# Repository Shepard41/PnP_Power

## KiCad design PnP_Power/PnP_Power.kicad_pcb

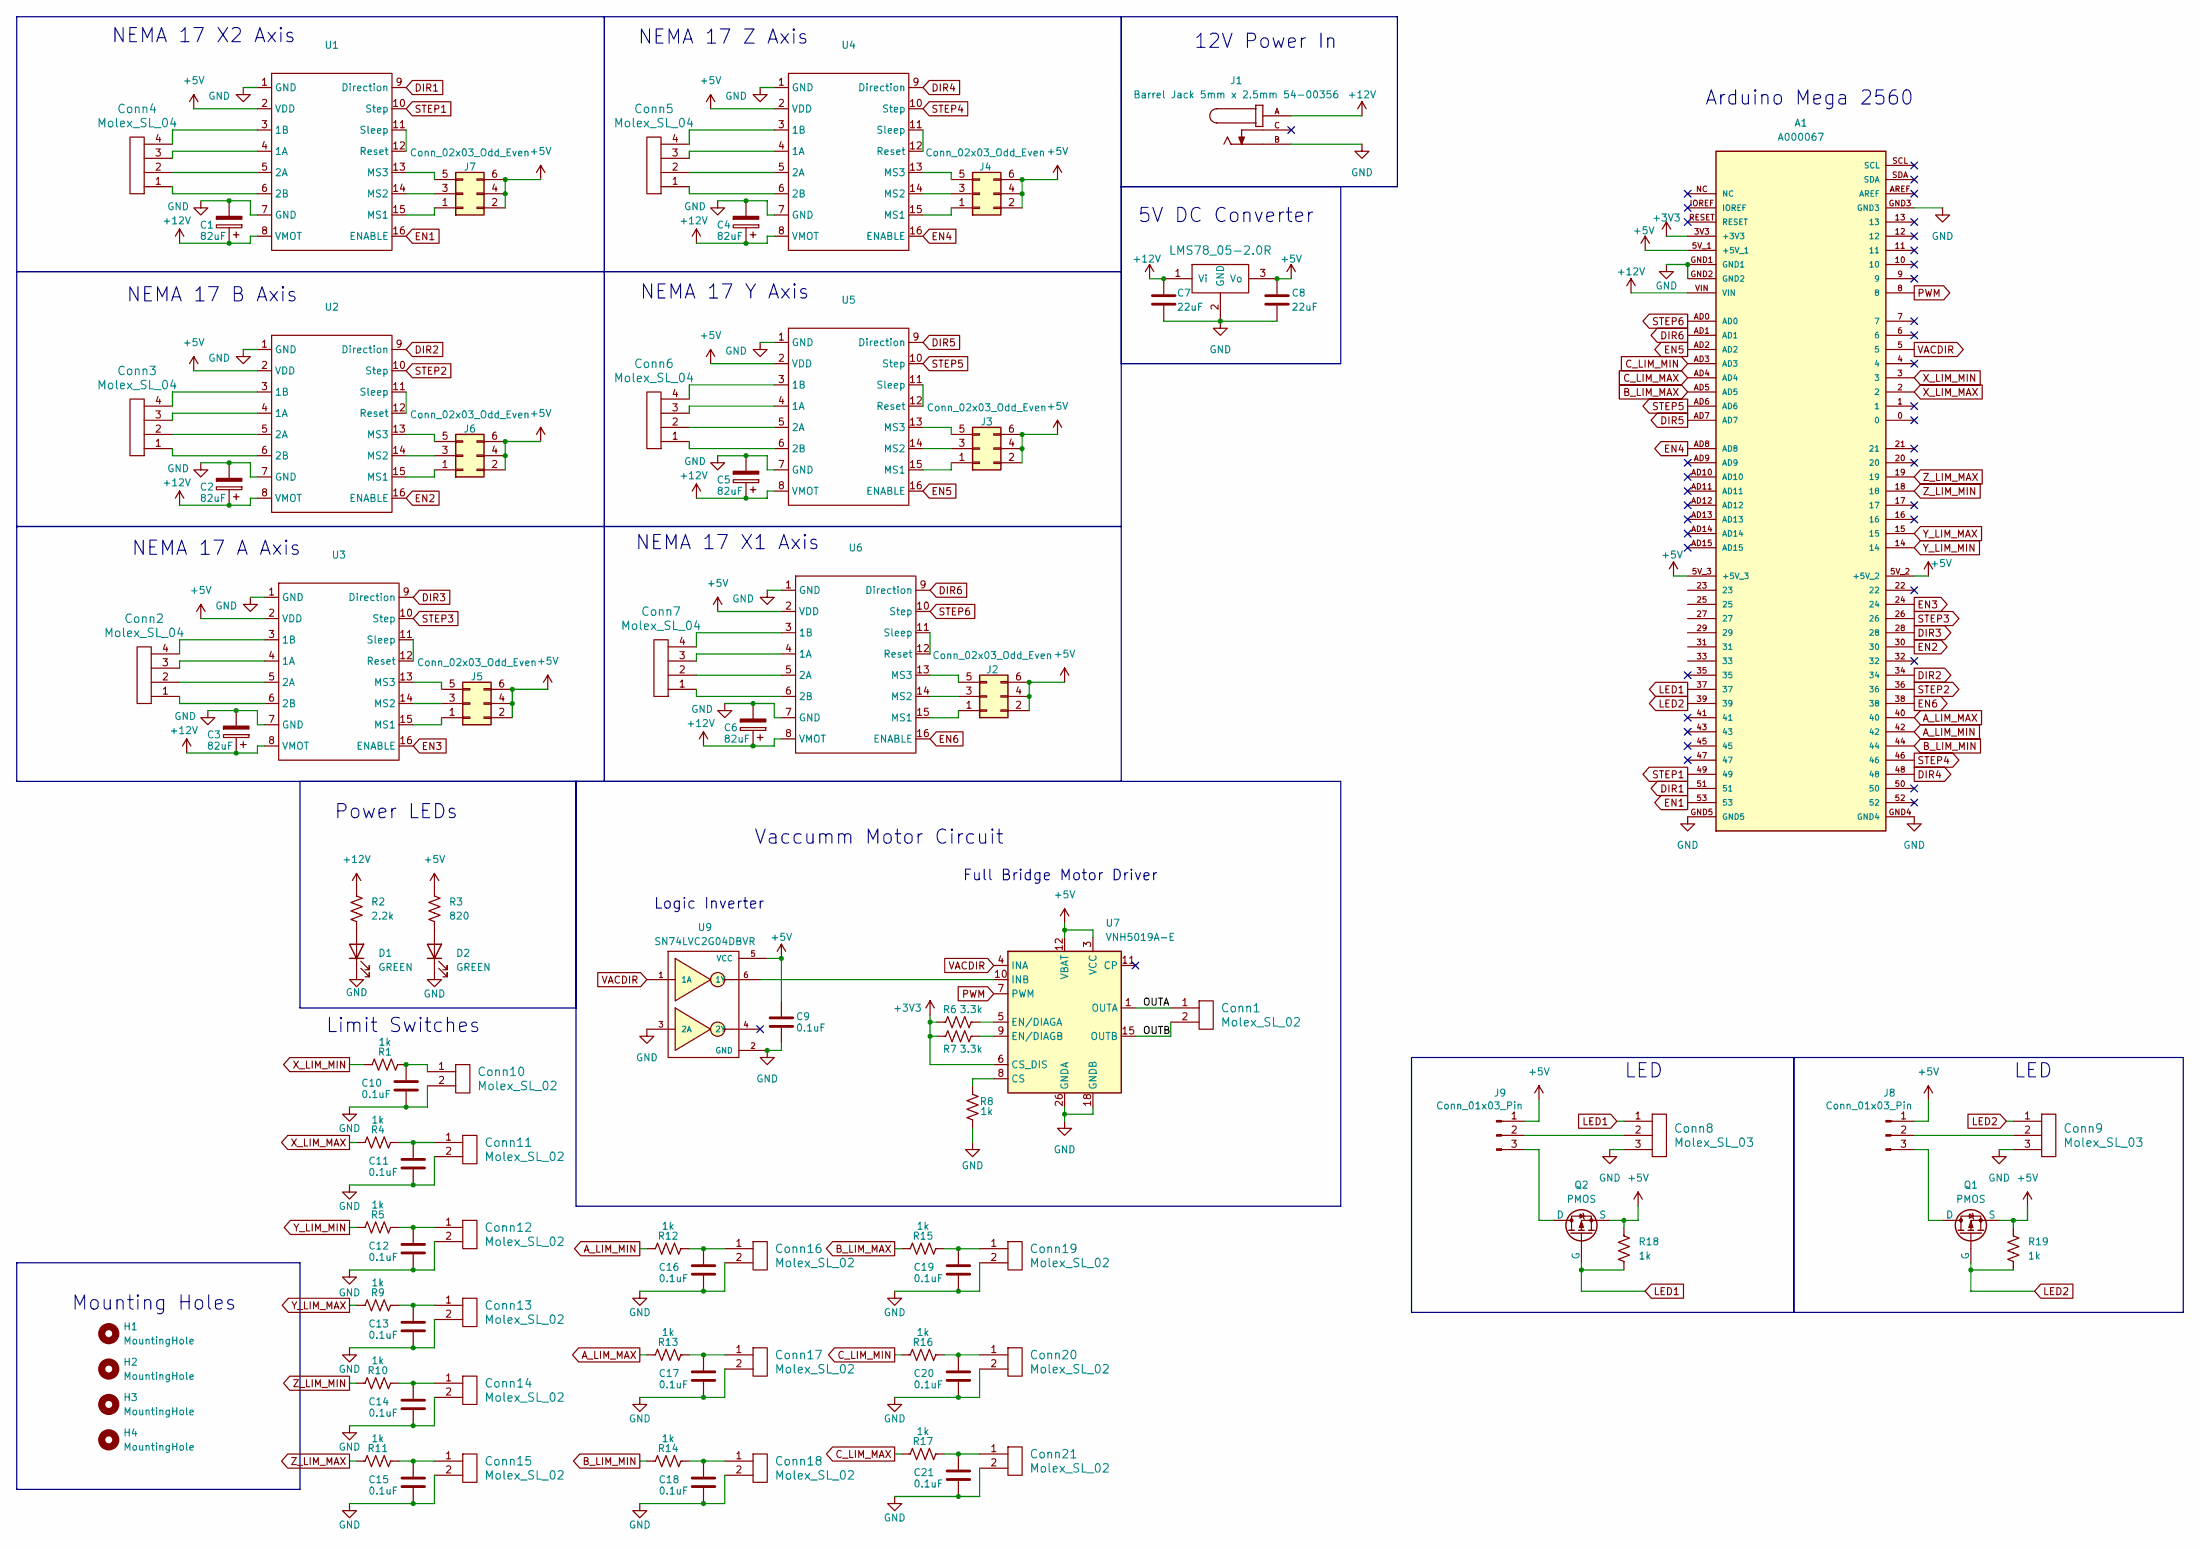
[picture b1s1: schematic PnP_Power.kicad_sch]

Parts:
A1: A000067; ARDUINO_A000067
C1, C2, C3, C4, C5, C6: 82uF; CP_Radial_D8.0mm_P3.50mm
C7, C8: 22uF; C_0603_1608Metric_Pad1.08x0.95mm_HandSolder
C9, C10, C11, C12, C13, C14, C15, C16, C17, C18, C19, C20, C21: 0.1uF; C_0603_1608Metric_Pad1.08x0.95mm_HandSolder
Conn1, Conn10, Conn11, Conn12, Conn13, Conn14, Conn15, Conn16, Conn17, Conn18, Conn19, Conn20, Conn21: Molex_SL_02; MOLEX_SL_02_Horizontal
Conn2, Conn3, Conn4, Conn5, Conn6, Conn7: Molex_SL_04; MOLEX_SL_04_Horizontal
Conn8, Conn9: Molex_SL_03; MOLEX_SL_03_Horizontal
D1, D2: GREEN; LED_0603_1608Metric_Pad1.05x0.95mm_HandSolder
H1, H2, H3, H4: MountingHole; MountingHole_2.2mm_M2
J1: Barrel Jack 5mm x 2.5mm 54-00356; TENSILITY_54-00356; PARTREV A
J2, J3, J4, J5, J6, J7: Conn_02x03_Odd_Even; PinHeader_2x03_P2.54mm_Vertical
J8, J9: Conn_01x03_Pin; PinHeader_1x03_P2.54mm_Vertical
Q1, Q2: PMOS; SOT-23; MPN SI2301-TP
R1, R4, R5, R8, R9, R10, R11, R12, R13, R14, R15, R16, R17, R18, R19: 1k; R_0603_1608Metric_Pad0.98x0.95mm_HandSolder
R2: 2.2k; R_0603_1608Metric_Pad0.98x0.95mm_HandSolder
R3: 820; R_0603_1608Metric_Pad0.98x0.95mm_HandSolder
R6, R7: 3.3k; R_0603_1608Metric_Pad0.98x0.95mm_HandSolder
U1, U2, U3, U4, U5, U6: A4988
U7: VNH5019A-E; ST_MultiPowerSO-30
U8: LMS78_05-2.0R
U9: SN74LVC2G04DBVR; SOT95P280X145-6N

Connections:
+3V3: A1.3V3 (+3V3), R6.2, R7.1, U7.6 (CS_DIS)
+5V: A1.5V_1 (+5V_1), A1.5V_2 (+5V_2), A1.5V_3 (+5V_3), C8.1, C9.1, J2.2, J2.4, J2.6, J3.2, J3.4, J3.6, J4.2, J4.4, J4.6, J5.2, J5.4, J5.6, J6.2, J6.4, J6.6, J7.2, J7.4, J7.6, J8.1, J9.1, Q1.2 (S), Q2.2 (S), R3.1, R18.1, R19.1, U1.2 (VDD), U2.2 (VDD), U3.2 (VDD), U4.2 (VDD), U5.2 (VDD), U6.2 (VDD), U7.3 (VCC), U7.12 (VBAT), U7.13 (VCC), U7.23 (VCC), U7.31 (VCC), U8.3 (Vo), U9.5 (VCC)
+12V: A1.VIN, C1.1, C2.1, C3.1, C4.1, C5.1, C6.1, C7.1, J1.A, R2.1, U1.8 (VMOT), U2.8 (VMOT), U3.8 (VMOT), U4.8 (VMOT), U5.8 (VMOT), U6.8 (VMOT), U8.1 (Vi)
/OUTA: Conn1.1, U7.1 (OUTA), U7.25 (OUTA), U7.30 (OUTA), U7.33 (OUTA)
/OUTB: Conn1.2, U7.15 (OUTB), U7.16 (OUTB), U7.21 (OUTB), U7.32 (OUTB)
DIR1: A1.51, U1.9 (Direction)
DIR2: A1.34, U2.9 (Direction)
DIR3: A1.28, U3.9 (Direction)
DIR4: A1.48, U4.9 (Direction)
DIR5: A1.AD7, U5.9 (Direction)
DIR6: A1.AD1, U6.9 (Direction)
EN1: A1.53, U1.16 (ENABLE)
EN2: A1.30, U2.16 (ENABLE)
EN3: A1.24, U3.16 (ENABLE)
EN4: A1.AD8, U4.16 (ENABLE)
EN5: A1.AD2, U5.16 (ENABLE)
EN6: A1.38, U6.16 (ENABLE)
GND: A1.GND1, A1.GND2, A1.GND3, A1.GND4, A1.GND5, C1.2, C2.2, C3.2, C4.2, C5.2, C6.2, C7.2, C8.2, C9.2, C10.2, C11.2, C12.2, C13.2, C14.2, C15.2, C16.2, C17.2, C18.2, C19.2, C20.2, C21.2, Conn8.3, Conn9.3, Conn10.2, Conn11.2, Conn12.2, Conn13.2, Conn14.2, Conn15.2, Conn16.2, Conn17.2, Conn18.2, Conn19.2, Conn20.2, Conn21.2, D1.1 (K), D2.1 (K), J1.B, R8.2, U1.1 (GND), U1.7 (GND), U2.1 (GND), U2.7 (GND), U3.1 (GND), U3.7 (GND), U4.1 (GND), U4.7 (GND), U5.1 (GND), U5.7 (GND), U6.1 (GND), U6.7 (GND), U7.18 (GNDB), U7.19 (GNDB), U7.20 (GNDB), U7.26 (GNDA), U7.27 (GNDA), U7.28 (GNDA), U8.2 (GND), U9.2 (GND), U9.3 (2A)
LED1: A1.37, Conn8.1, Q2.1 (G), R18.2
LED2: A1.39, Conn9.1, Q1.1 (G), R19.2
LS1: A1.3, R1.1
LS2: A1.2, R4.1
LS3: A1.14, R5.1
LS4: A1.15, R9.1
LS5: A1.18, R10.1
LS6: A1.19, R11.1
LS7: A1.42, R12.1
LS8: A1.40, R13.1
LS9: A1.44, R14.1
LS10: A1.AD5, R15.1
LS11: A1.AD3, R16.1
LS12: A1.AD4, R17.1
unnamed: C10.1, Conn10.1, R1.2
unnamed: C11.1, Conn11.1, R4.2
unnamed: C12.1, Conn12.1, R5.2
unnamed: C13.1, Conn13.1, R9.2
unnamed: C14.1, Conn14.1, R10.2
unnamed: C15.1, Conn15.1, R11.2
unnamed: C16.1, Conn16.1, R12.2
unnamed: C17.1, Conn17.1, R13.2
unnamed: C18.1, Conn18.1, R14.2
unnamed: C19.1, Conn19.1, R15.2
unnamed: C20.1, Conn20.1, R16.2
unnamed: C21.1, Conn21.1, R17.2
unnamed: D1.2 (A), R2.2
unnamed: D2.2 (A), R3.2
unnamed: J2.1, U6.15 (MS1)
unnamed: J2.3, U6.14 (MS2)
unnamed: J2.5, U6.13 (MS3)
unnamed: J3.1, U5.15 (MS1)
unnamed: J3.3, U5.14 (MS2)
unnamed: J3.5, U5.13 (MS3)
unnamed: J4.1, U4.15 (MS1)
unnamed: J4.3, U4.14 (MS2)
unnamed: J4.5, U4.13 (MS3)
unnamed: J5.1, U3.15 (MS1)
unnamed: J5.3, U3.14 (MS2)
unnamed: J5.5, U3.13 (MS3)
unnamed: J6.1, U2.15 (MS1)
unnamed: J6.3, U2.14 (MS2)
unnamed: J6.5, U2.13 (MS3)
unnamed: J7.1, U1.15 (MS1)
unnamed: J7.3, U1.14 (MS2)
unnamed: J7.5, U1.13 (MS3)
unnamed: Conn9.2, J8.2
unnamed: J8.3, Q1.3 (D)
unnamed: Conn8.2, J9.2
unnamed: J9.3, Q2.3 (D)
unnamed: Conn4.3, U1.4 (1A)
unnamed: Conn4.4, U1.3 (1B)
unnamed: Conn4.2, U1.5 (2A)
unnamed: Conn4.1, U1.6 (2B)
unnamed: U1.11 (Sleep), U1.12 (Reset)
unnamed: Conn3.3, U2.4 (1A)
unnamed: Conn3.4, U2.3 (1B)
unnamed: Conn3.2, U2.5 (2A)
unnamed: Conn3.1, U2.6 (2B)
unnamed: U2.11 (Sleep), U2.12 (Reset)
unnamed: Conn2.3, U3.4 (1A)
unnamed: Conn2.4, U3.3 (1B)
unnamed: Conn2.2, U3.5 (2A)
unnamed: Conn2.1, U3.6 (2B)
unnamed: U3.11 (Sleep), U3.12 (Reset)
unnamed: Conn5.3, U4.4 (1A)
unnamed: Conn5.4, U4.3 (1B)
unnamed: Conn5.2, U4.5 (2A)
unnamed: Conn5.1, U4.6 (2B)
unnamed: U4.11 (Sleep), U4.12 (Reset)
unnamed: Conn6.3, U5.4 (1A)
unnamed: Conn6.4, U5.3 (1B)
unnamed: Conn6.2, U5.5 (2A)
unnamed: Conn6.1, U5.6 (2B)
unnamed: U5.11 (Sleep), U5.12 (Reset)
unnamed: Conn7.3, U6.4 (1A)
unnamed: Conn7.4, U6.3 (1B)
unnamed: Conn7.2, U6.5 (2A)
unnamed: Conn7.1, U6.6 (2B)
unnamed: U6.11 (Sleep), U6.12 (Reset)
unnamed: R8.1, U7.8 (CS)
unnamed: R6.1, U7.5 (EN/DIAGA)
unnamed: R7.2, U7.9 (EN/DIAGB)
unnamed: U7.10 (INB), U9.6 (1Y)
PWM: A1.8, U7.7 (PWM)
STEP1: A1.49, U1.10 (Step)
STEP2: A1.36, U2.10 (Step)
STEP3: A1.26, U3.10 (Step)
STEP4: A1.46, U4.10 (Step)
STEP5: A1.AD6, U5.10 (Step)
STEP6: A1.AD0, U6.10 (Step)
VACDIR: A1.5, U7.4 (INA), U9.1 (1A)

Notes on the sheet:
5V DC Converter
LED
Mounting Holes
12V Power In
Limit Switches
Full Bridge Motor Driver
Vaccumm Motor Circuit
NEMA 17 X2 Axis
NEMA 17 B Axis
NEMA 17 Z Axis
NEMA 17 A Axis
Arduino Mega 2560
Power LEDs
NEMA 17 X1 Axis
Logic Inverter
NEMA 17 Y Axis

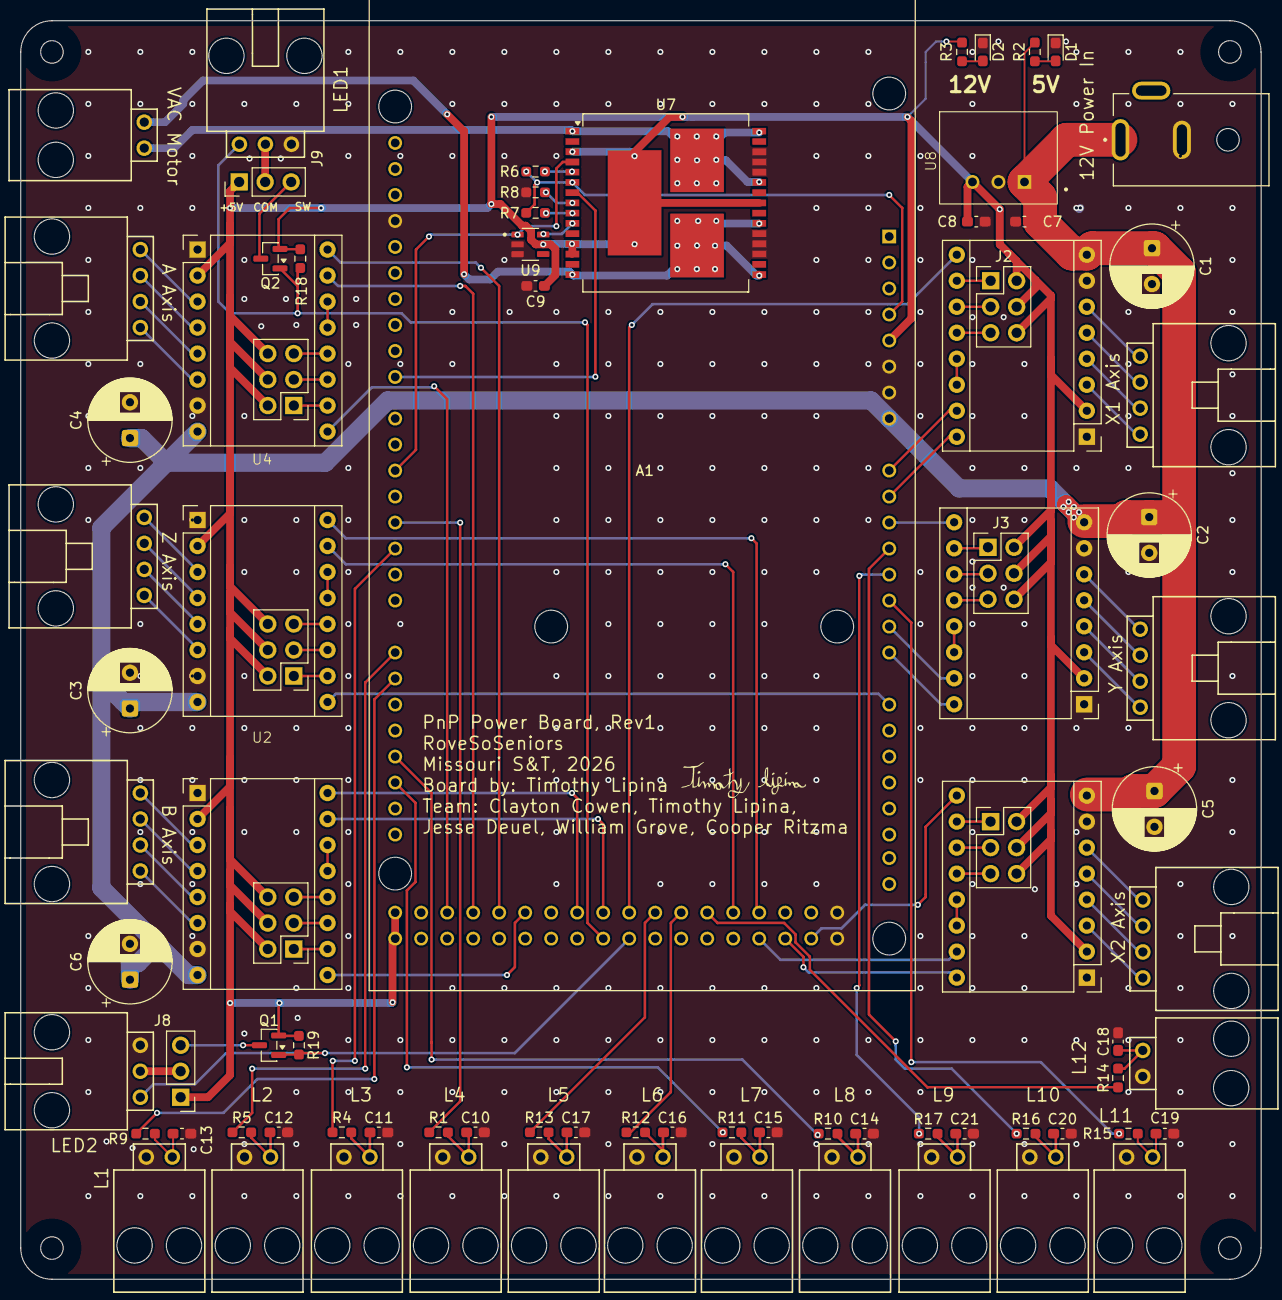
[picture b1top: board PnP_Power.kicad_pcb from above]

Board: 2 copper layers, 121.2 x 122.9 mm, 88 parts (0 on the bottom side), 110 nets.

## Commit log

2025-11-16 Started Project
2025-11-16 Made symbol
2026-02-12 Symbol and Footprint import
2026-02-16 Started
2026-02-16 Progress
    Schematic has everything but 12V jack and H-bridge Vac DC motor control
2026-02-19 Connectors changed, H-bridge VNH added, white leds done
2026-03-04 Schematic and Layout Changes
    updated schematic logic
    added limit switches
    added 12V to 5V dc converter
    added power jack
    added jumpers
    added inverter for DIRSW
2026-03-06 Idek
    layouts and stuff and 3d model
2026-03-14 Routed and Labeled layout
2026-03-14 Added some datasheets and silkscreens
2026-03-15 Minor changes
2026-03-19 Many things
2026-03-19 Some changes from doc
2026-03-19 Fix DRC issues
2026-03-19 Done
2026-03-19 Final board trust me
2026-04-05 Fix bad file naming.
